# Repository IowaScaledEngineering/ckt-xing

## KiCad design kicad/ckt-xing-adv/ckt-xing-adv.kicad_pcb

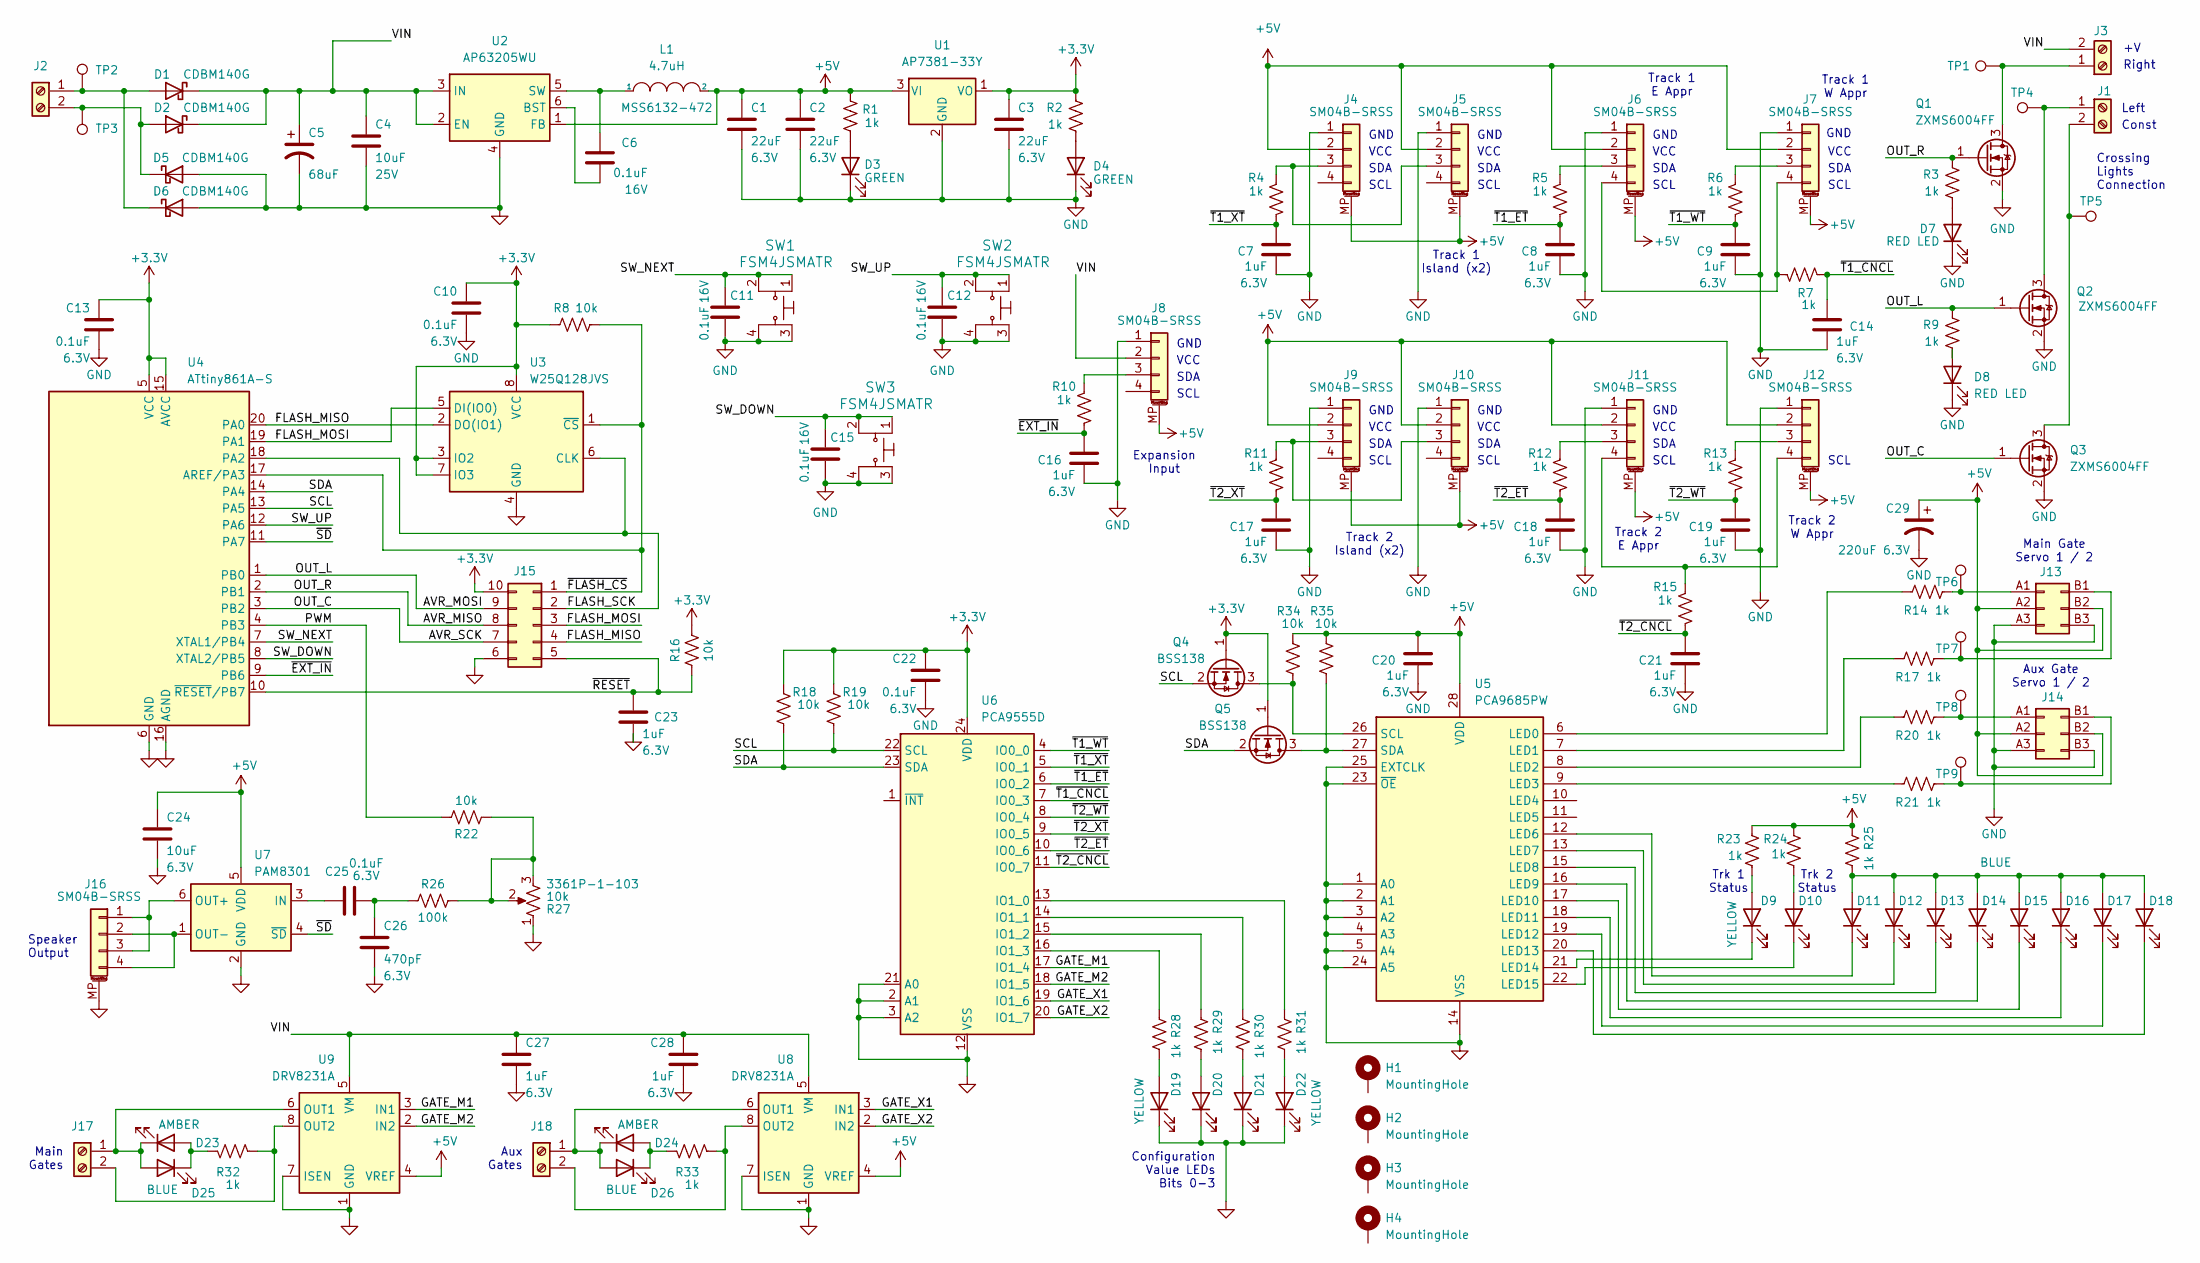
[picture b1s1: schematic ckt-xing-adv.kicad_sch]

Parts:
C1, C2, C3: 22uF; C_0805_2012Metric; Voltage 6.3V
C4: 10uF; C_0805_2012Metric; Voltage 25V
C5: 68uF; CP_Elec_6.3x5.8
C6, C11, C12, C15: 0.1uF; C_0805_2012Metric; Voltage 16V
C7, C8, C9, C14, C16, C17, C18, C19, C20, C21, C23, C27, C28: 1uF; C_0805_2012Metric; Voltage 6.3V
C10, C13, C22, C25: 0.1uF; C_0805_2012Metric; Voltage 6.3V
C24: 10uF; C_0805_2012Metric; Voltage 6.3V
C26: 470pF; C_0805_2012Metric; Voltage 6.3V
C29: 220uF 6.3V; CP_Elec_6.3x5.8
D1, D2, D5, D6: CDBM140G; SOD-123T
D3, D4: GREEN; LED_0805_2012Metric
D7, D8: RED LED; LED_0805_2012Metric
D9, D10, D11, D12, D13, D14, D16, D17, D18, D19, D20, D21, D22: YELLOW; LED_0805_2012Metric
D15, D25, D26: BLUE; LED_0805_2012Metric
D23, D24: AMBER; LED_0805_2012Metric
H1, H2, H3, H4: MountingHole; MountingHole_3.2mm_M3_Pad
J1, J2, J3, J17, J18: Screw_Terminal_01x02; TerminalBlock_RND_205-00012_1x02_P5.00mm_Horizontal
J4, J5, J6, J7, J8, J9, J10, J11, J12, J16: SM04B-SRSS; JST_SH_SM04B-SRSS-TB_1x04-1MP_P1.00mm_Horizontal
J13, J14: Conn_02x03_Row_Letter_First; MOLEX_15910060
J15: Conn_02x05_Counter_Clockwise; Tag-Connect_TC2050-IDC-FP_2x05_P1.27mm_Vertical
L1: 4.7uH; MSS6132-xxxMLC
Q1, Q2, Q3: ZXMS6004FF; SOT-23
Q4, Q5: BSS138; SOT-23
R1, R2, R3, R4, R5, R6, R7, R9, R10, R11, R12, R13, R14, R15, R17, R20, R21, R23, R24, R25, R28, R29, R30, R31, R32, R33: 1k; R_0805_2012Metric
R8, R16, R18, R19, R22, R34, R35: 10k; R_0805_2012Metric
R26: 100k; R_0805_2012Metric
R27: 10k; POT_3361P_BRN
SW1, SW2, SW3: FSM4JSMATR; TE_FSM4JSMA; MPN FSM4JSMATR; Digi-Key_PN 450-1759-1-ND
TP1, TP2, TP3, TP4, TP5, TP6, TP7, TP8, TP9: TestPoint; TestPoint_Pad_D2.0mm
U1: AP7381-33Y; SOT-89-3
U2: AP63205WU; TSOT-23-6
U3: W25Q128JVS; SOIC-8_5.3x6.2mm_P1.27mm
U4: ATtiny861A-S; SOIC-20W_7.5x12.8mm_P1.27mm
U5: PCA9685PW; TSSOP-28_4.4x9.7mm_P0.65mm
U6: PCA9555D; TSSOP-24_4.4x7.8mm_P0.65mm
U7: PAM8301; SOT-23-6
U8, U9: DRV8231A; Texas_HTSOP-8-1EP_3.9x4.9mm_P1.27mm_EP2.95x4.9mm_Mask2.4x3.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

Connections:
+3.3V: C3.1, C10.1, C13.1, C22.1, J15.10, Q4.1 (G), Q5.1 (G), R2.2, R8.1, R16.2, R18.2, R19.2, U1.1 (VO), U3.3 (IO2), U3.7 (IO3), U3.8 (VCC), U4.5 (VCC), U4.15 (AVCC), U6.24 (VDD)
+5V: C1.1, C2.1, C20.1, C24.1, C29.1, J4.2, J4.MP (MountPin), J5.2, J5.MP (MountPin), J6.2, J6.MP (MountPin), J7.2, J7.MP (MountPin), J8.MP (MountPin), J9.2, J9.MP (MountPin), J10.2, J10.MP (MountPin), J11.2, J11.MP (MountPin), J12.2, J12.MP (MountPin), J13.A2 (Pin_a2), J13.B2 (Pin_b2), J14.A2 (Pin_a2), J14.B2 (Pin_b2), L1.2, R1.2, R23.1, R24.1, R25.1, R34.2, R35.2, U1.3 (VI), U2.1 (FB), U5.28 (VDD), U7.5 (VDD), U8.4 (VREF), U9.4 (VREF)
/AVR_MISO: J15.8, Q1.1 (G), R3.2, U4.2 (PB1)
/AVR_MOSI: J15.9, Q2.1 (G), R9.2, U4.1 (PB0)
/AVR_SCK: J15.7, Q3.1 (G), U4.3 (PB2)
/FLASH_MISO: J15.4, U3.2 (DO(IO1)), U4.20 (PA0)
/FLASH_MOSI: J15.3, U3.5 (DI(IO0)), U4.19 (PA1)
/FLASH_SCK: J15.2, U3.6 (CLK), U4.18 (PA2)
/GATE_M1: U6.17 (IO1_4), U9.3 (IN1)
/GATE_M2: U6.18 (IO1_5), U9.2 (IN2)
/GATE_X1: U6.19 (IO1_6), U8.3 (IN1)
/GATE_X2: U6.20 (IO1_7), U8.2 (IN2)
/PWM: R22.2, U4.4 (PB3)
/SCL: Q4.2 (S), R19.1, U4.13 (PA5), U6.22 (SCL)
/SDA: Q5.2 (S), R18.1, U4.14 (PA4), U6.23 (SDA)
/SW_DOWN: C15.1, SW3.1, SW3.2, U4.8 (XTAL2/PB5)
/SW_NEXT: C11.1, SW1.1, SW1.2, U4.7 (XTAL1/PB4)
/SW_UP: C12.1, SW2.1, SW2.2, U4.12 (PA6)
/VIN: C4.1, C5.1, C27.1, C28.1, D1.1 (K), D2.1 (K), J3.2, J8.2, U2.2 (EN), U2.3 (IN), U8.5 (VM), U9.5 (VM)
/~EXT_IN: C16.1, R10.2, U4.9 (PB6)
/~FLASH_CS: J15.1, R8.2, U3.1 (~CS), U4.17 (AREF/PA3)
/~RESET: C23.1, J15.5, R16.1, U4.10 (~RESET/PB7)
/~SD: U4.11 (PA7), U7.4 (~SD)
/~T1_CNCL: C14.1, R7.2, U6.7 (IO0_3)
/~T1_ET: C8.1, R5.2, U6.6 (IO0_2)
/~T1_WT: C9.1, R6.2, U6.4 (IO0_0)
/~T1_XT: C7.1, R4.2, U6.5 (IO0_1)
/~T2_CNCL: C21.1, R15.2, U6.11 (IO0_7)
/~T2_ET: C18.1, R12.2, U6.10 (IO0_6)
/~T2_WT: C19.1, R13.2, U6.8 (IO0_4)
/~T2_XT: C17.1, R11.2, U6.9 (IO0_5)
GND: C1.2, C2.2, C3.2, C4.2, C5.2, C7.2, C8.2, C9.2, C10.2, C11.2, C12.2, C13.2, C14.2, C15.2, C16.2, C17.2, C18.2, C19.2, C20.2, C21.2, C22.2, C23.2, C24.2, C26.2, C27.2, C28.2, C29.2, D3.1 (K), D4.1 (K), D5.2 (A), D6.2 (A), D7.1 (K), D8.1 (K), D19.1 (K), D20.1 (K), D21.1 (K), D22.1 (K), J4.1, J5.1, J6.1, J7.1, J8.1, J9.1, J10.1, J11.1, J12.1, J13.A3 (Pin_a3), J13.B3 (Pin_b3), J14.A3 (Pin_a3), J14.B3 (Pin_b3), J15.6, J16.MP (MountPin), Q1.2 (S), Q2.2 (S), Q3.2 (S), R27.1, SW1.3, SW1.4, SW2.3, SW2.4, SW3.3, SW3.4, U1.2 (GND), U2.4 (GND), U3.4 (GND), U4.6 (GND), U4.16 (AGND), U5.1 (A0), U5.2 (A1), U5.3 (A2), U5.4 (A3), U5.5 (A4), U5.14 (VSS), U5.23 (~OE), U5.24 (A5), U5.25 (EXTCLK), U6.2 (A1), U6.3 (A2), U6.12 (VSS), U6.21 (A0), U7.2 (GND), U8.1 (GND), U8.7 (ISEN), U8.9 (GND), U9.1 (GND), U9.7 (ISEN), U9.9 (GND)
unnamed: C25.2, C26.1, R26.1
unnamed: D1.2 (A), D6.1 (K), J2.1, TP2.1
unnamed: D2.2 (A), D5.1 (K), J2.2, TP3.1
unnamed: D3.2 (A), R1.1
unnamed: D4.2 (A), R2.1
unnamed: D7.2 (A), R3.1
unnamed: D8.2 (A), R9.1
unnamed: D9.2 (A), R23.2
unnamed: D9.1 (K), U5.21 (LED14)
unnamed: D10.2 (A), R24.2
unnamed: D10.1 (K), U5.22 (LED15)
unnamed: D11.2 (A), D12.2 (A), D13.2 (A), D14.2 (A), D15.2 (A), D16.2 (A), D17.2 (A), D18.2 (A), R25.2
unnamed: D11.1 (K), U5.12 (LED6)
unnamed: D12.1 (K), U5.13 (LED7)
unnamed: D13.1 (K), U5.15 (LED8)
unnamed: D14.1 (K), U5.16 (LED9)
unnamed: D15.1 (K), U5.17 (LED10)
unnamed: D16.1 (K), U5.18 (LED11)
unnamed: D17.1 (K), U5.19 (LED12)
unnamed: D18.1 (K), U5.20 (LED13)
unnamed: D19.2 (A), R28.2
unnamed: D20.2 (A), R29.2
unnamed: D21.2 (A), R30.2
unnamed: D22.2 (A), R31.2
unnamed: D23.2 (A), D25.1 (K), R32.1
unnamed: D23.1 (K), D25.2 (A), J17.1, U9.6 (OUT1)
unnamed: D24.2 (A), D26.1 (K), R33.1
unnamed: D24.1 (K), D26.2 (A), J18.1, U8.6 (OUT1)
unnamed: J1.1, Q2.3 (D), TP4.1
unnamed: J1.2, Q3.3 (D), TP5.1
unnamed: J3.1, Q1.3 (D), TP1.1
unnamed: J4.3, J5.3, R4.1
unnamed: J6.3, R5.1
unnamed: J6.4, J7.4, R7.1
unnamed: J7.3, R6.1
unnamed: J8.3, R10.1
unnamed: J9.3, J10.3, R11.1
unnamed: J11.3, R12.1
unnamed: J11.4, J12.4, R15.1
unnamed: J12.3, R13.1
unnamed: J13.A1 (Pin_a1), R14.2, TP6.1
unnamed: J13.B1 (Pin_b1), R17.2, TP7.1
unnamed: J14.A1 (Pin_a1), R20.2, TP8.1
unnamed: J14.B1 (Pin_b1), R21.2, TP9.1
unnamed: J16.1, J16.3, U7.6 (OUT+)
unnamed: J16.2, J16.4, U7.1 (OUT-)
unnamed: J17.2, R32.2, U9.8 (OUT2)
unnamed: J18.2, R33.2, U8.8 (OUT2)
unnamed: Q4.3 (D), R34.1, U5.26 (SCL)
unnamed: Q5.3 (D), R35.1, U5.27 (SDA)
unnamed: R22.1, R26.2, R27.2, R27.3
unnamed: C6.2, U2.6 (BST)
unnamed: C6.1, L1.1, U2.5 (SW)
unnamed: R14.1, U5.6 (LED0)
unnamed: R17.1, U5.7 (LED1)
unnamed: R20.1, U5.8 (LED2)
unnamed: R21.1, U5.9 (LED3)
unnamed: R31.1, U6.13 (IO1_0)
unnamed: R30.1, U6.14 (IO1_1)
unnamed: R29.1, U6.15 (IO1_2)
unnamed: R28.1, U6.16 (IO1_3)
unnamed: C25.1, U7.3 (IN)

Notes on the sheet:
SDA
Track 1 E Appr
Const
SCL
Trk 2 Status
GND
Speaker Output
Track 1 W Appr
Aux Gates
VCC
Track 1 Island (x2)
Left
Crossing Lights Connection
Trk 1 Status
Configuration Value LEDs Bits 0-3
Track 2 E Appr
Aux Gate Servo 1 / 2
Expansion Input
Main Gates
Track 2 W Appr
Right
Track 2 Island (x2)
Main Gate Servo 1 / 2

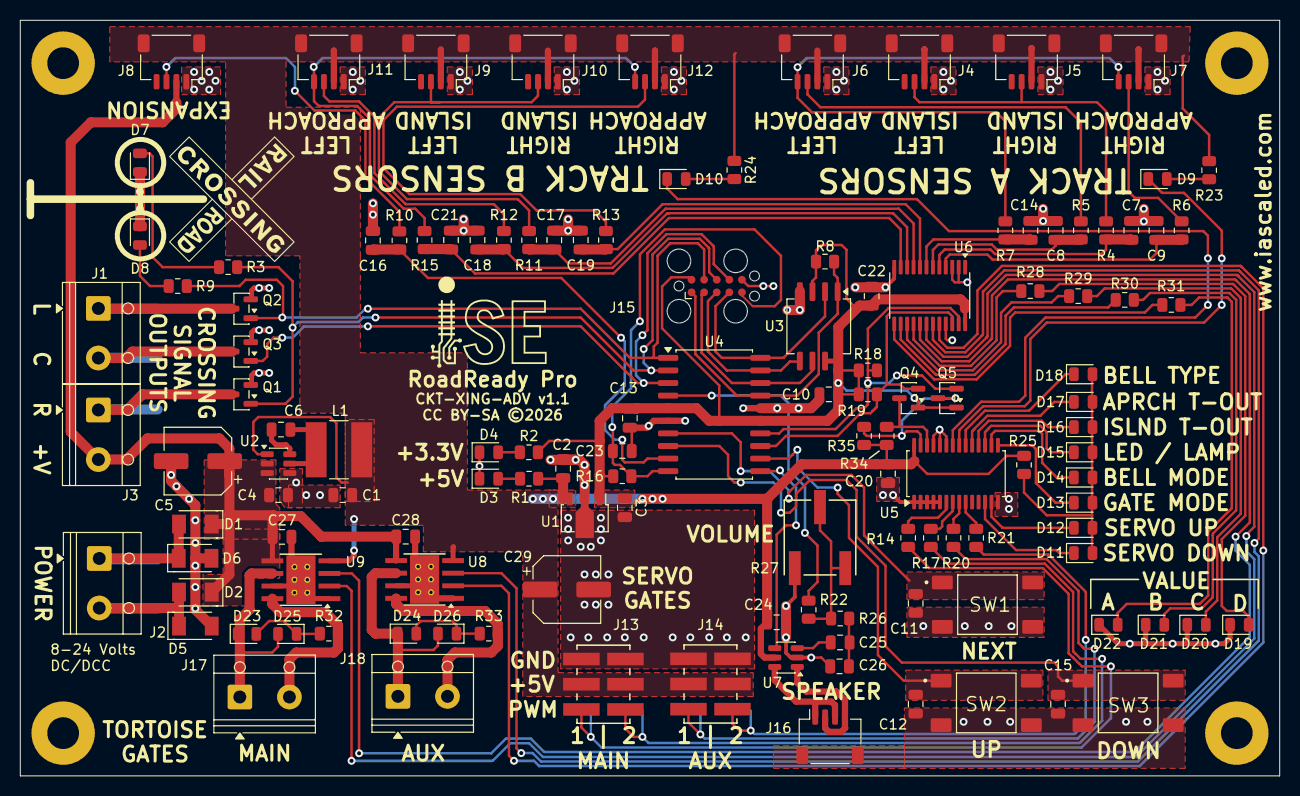
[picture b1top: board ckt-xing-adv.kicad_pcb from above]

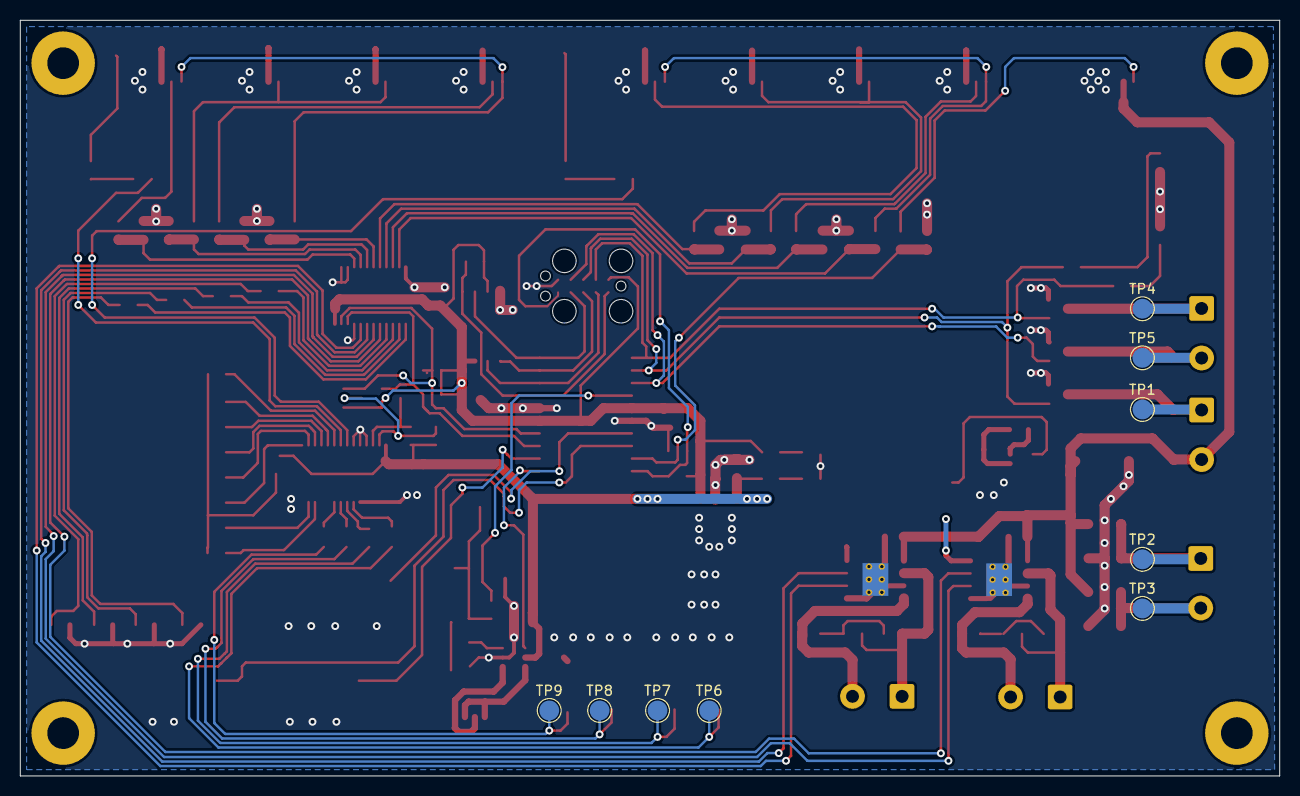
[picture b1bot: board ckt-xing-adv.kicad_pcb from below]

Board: 2 copper layers, 127.0 x 76.2 mm, 139 parts (9 on the bottom side), 94 nets.

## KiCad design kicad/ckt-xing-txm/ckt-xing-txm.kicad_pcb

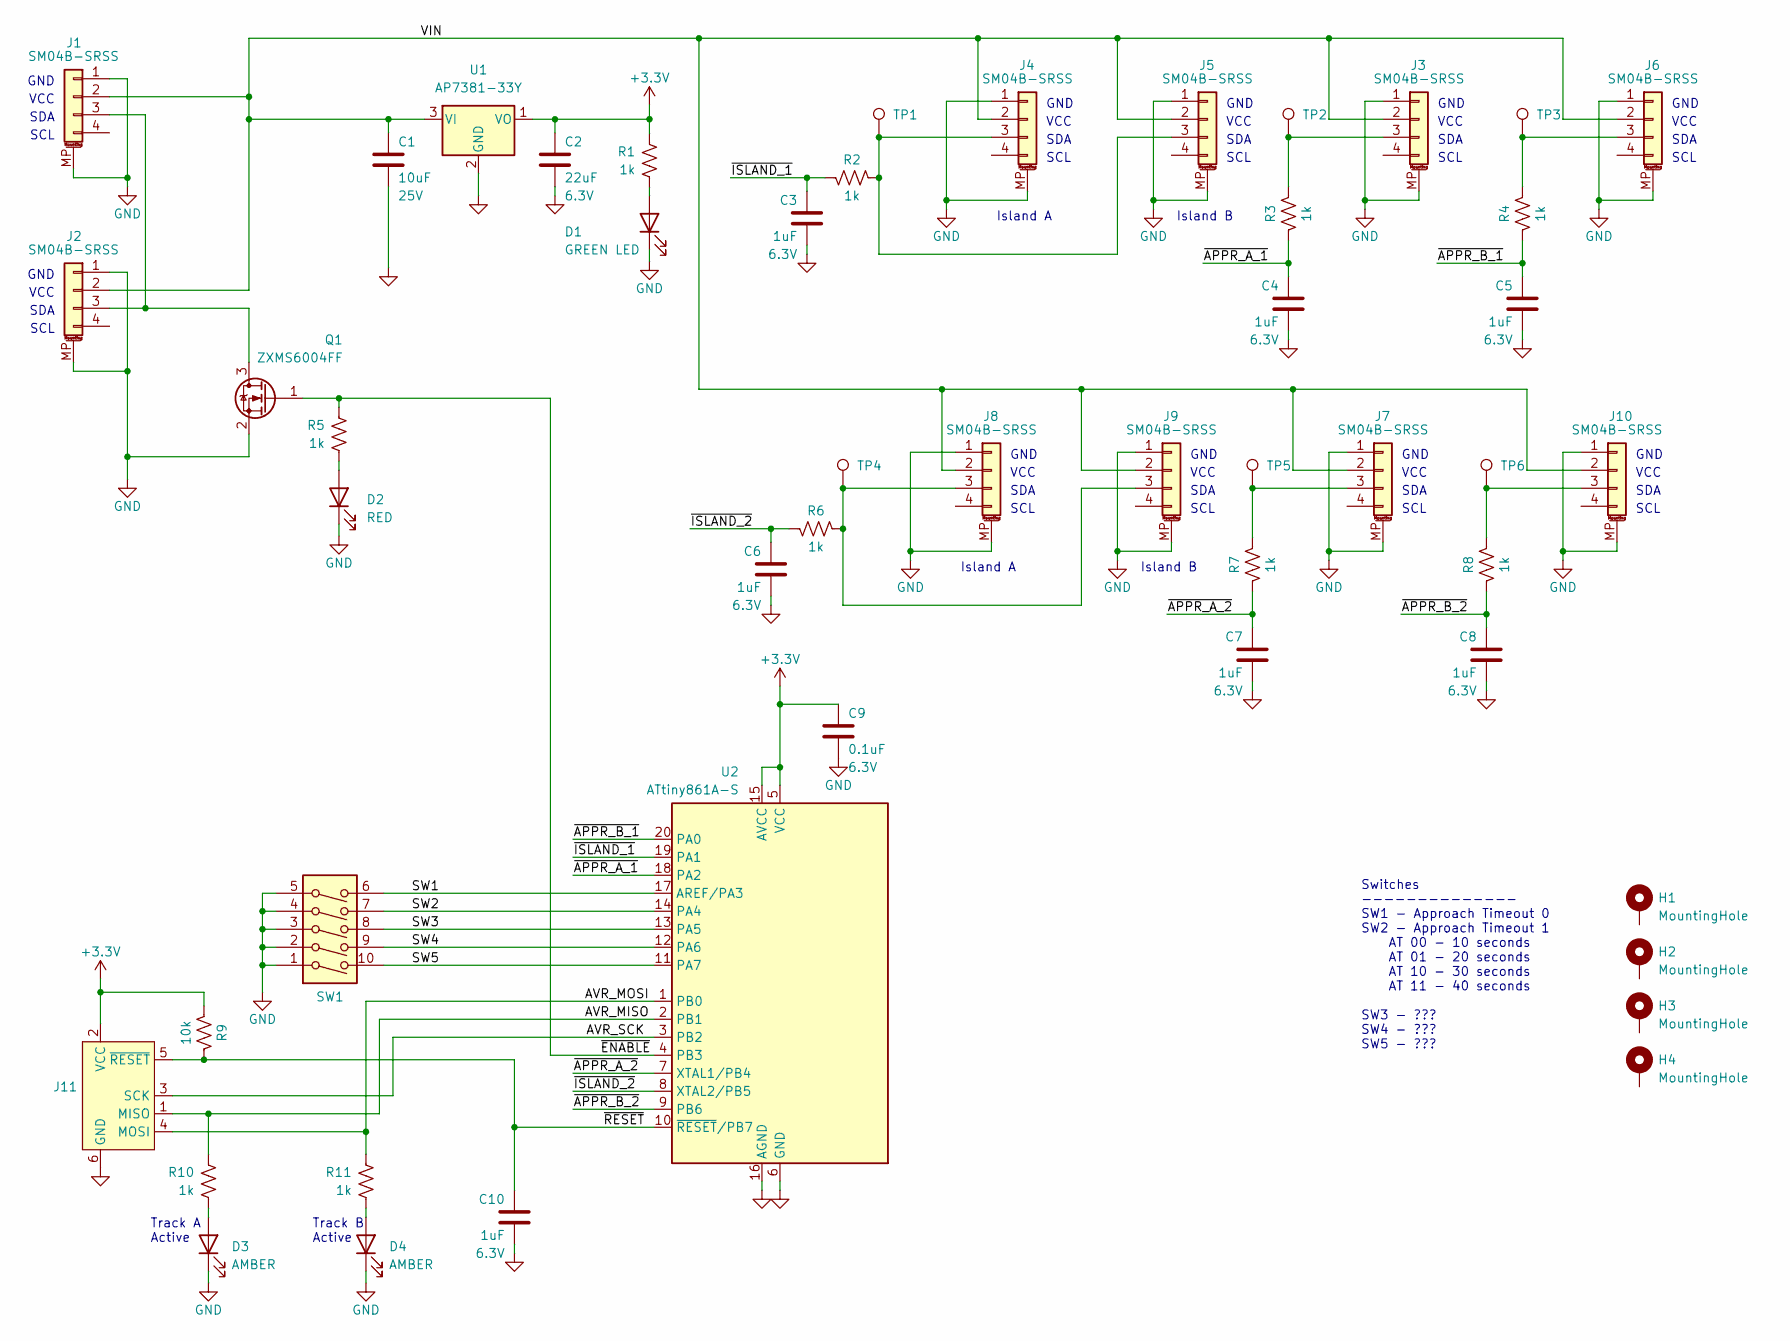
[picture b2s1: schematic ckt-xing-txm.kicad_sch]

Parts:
C1: 10uF; C_0805_2012Metric; Voltage 25V
C2: 22uF; C_0805_2012Metric; Voltage 6.3V
C3, C4, C5, C6, C7, C8, C10: 1uF; C_0805_2012Metric; Voltage 6.3V
C9: 0.1uF; C_0805_2012Metric; Voltage 6.3V
D1: GREEN LED; LED_0805_2012Metric
D2: RED; LED_0805_2012Metric
D3, D4: AMBER; LED_0805_2012Metric
H1, H2, H3, H4: MountingHole; MountingHole_3.2mm_M3_Pad
J1, J2, J3, J4, J5, J6, J7, J8, J9, J10: SM04B-SRSS; JST_SH_SM04B-SRSS-TB_1x04-1MP_P1.00mm_Horizontal
J11: Conn_AVR_TagConnect_TC2030; Tag-Connect_TC2030-IDC-NL_2x03_P1.27mm_Vertical
Q1: ZXMS6004FF; SOT-23
R1, R2, R3, R4, R5, R6, R7, R8, R10, R11: 1k; R_0805_2012Metric
R9: 10k; R_0805_2012Metric
SW1: SW_DIP_x05; CST_219SMT
TP1, TP2, TP3, TP4, TP5, TP6: TestPoint; TestPoint_Pad_D2.0mm
U1: AP7381-33Y; SOT-89-3
U2: ATtiny861A-S; SOIC-20W_7.5x12.8mm_P1.27mm

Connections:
+3.3V: C2.1, C9.1, J11.2 (VCC), R1.2, R9.2, U1.1 (VO), U2.5 (VCC), U2.15 (AVCC)
/AVR_MISO: J11.1 (MISO), R10.2, U2.2 (PB1)
/AVR_MOSI: J11.4 (MOSI), R11.2, U2.1 (PB0)
/AVR_SCK: J11.3 (SCK), U2.3 (PB2)
/SW1: SW1.6, U2.17 (AREF/PA3)
/SW2: SW1.7, U2.14 (PA4)
/SW3: SW1.8, U2.13 (PA5)
/SW4: SW1.9, U2.12 (PA6)
/SW5: SW1.10, U2.11 (PA7)
/VIN: C1.1, J1.2, J2.2, J3.2, J4.2, J5.2, J6.2, J7.2, J8.2, J9.2, J10.2, U1.3 (VI)
/~APPR_A_1: C4.1, R3.2, U2.18 (PA2)
/~APPR_A_2: C7.1, R7.2, U2.7 (XTAL1/PB4)
/~APPR_B_1: C5.1, R4.2, U2.20 (PA0)
/~APPR_B_2: C8.1, R8.2, U2.9 (PB6)
/~ENABLE: Q1.1 (G), R5.2, U2.4 (PB3)
/~ISLAND_1: C3.1, R2.2, U2.19 (PA1)
/~ISLAND_2: C6.1, R6.2, U2.8 (XTAL2/PB5)
/~RESET: C10.1, J11.5 (~RESET), R9.1, U2.10 (~RESET/PB7)
GND: C1.2, C2.2, C3.2, C4.2, C5.2, C6.2, C7.2, C8.2, C9.2, C10.2, D1.1 (K), D2.1 (K), D3.1 (K), D4.1 (K), J1.1, J1.MP (MountPin), J2.1, J2.MP (MountPin), J3.1, J3.MP (MountPin), J4.1, J4.MP (MountPin), J5.1, J5.MP (MountPin), J6.1, J6.MP (MountPin), J7.1, J7.MP (MountPin), J8.1, J8.MP (MountPin), J9.1, J9.MP (MountPin), J10.1, J10.MP (MountPin), J11.6 (GND), Q1.2 (S), SW1.1, SW1.2, SW1.3, SW1.4, SW1.5, U1.2 (GND), U2.6 (GND), U2.16 (AGND)
unnamed: D1.2 (A), R1.1
unnamed: D2.2 (A), R5.1
unnamed: D3.2 (A), R10.1
unnamed: D4.2 (A), R11.1
unnamed: J1.3, J2.3, Q1.3 (D)
unnamed: J3.3, R3.1, TP2.1
unnamed: J6.3, R4.1, TP3.1
unnamed: J7.3, R7.1, TP5.1
unnamed: J8.3, J9.3, R6.1, TP4.1
unnamed: J10.3, R8.1, TP6.1
unnamed: J4.3, J5.3, R2.1, TP1.1

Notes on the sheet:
SCL
Track A Active
GND
VCC
SDA
Island B
Island A
Switches -------------- SW1 - Approach Timeout 0 SW2 - Approach Timeout 1 AT 00 - 10 seconds AT 01 - 20 seconds AT 10 - 30 seconds AT 11 - 40 seconds SW3 - ??? SW4 - ??? SW5 - ???
Track B Active

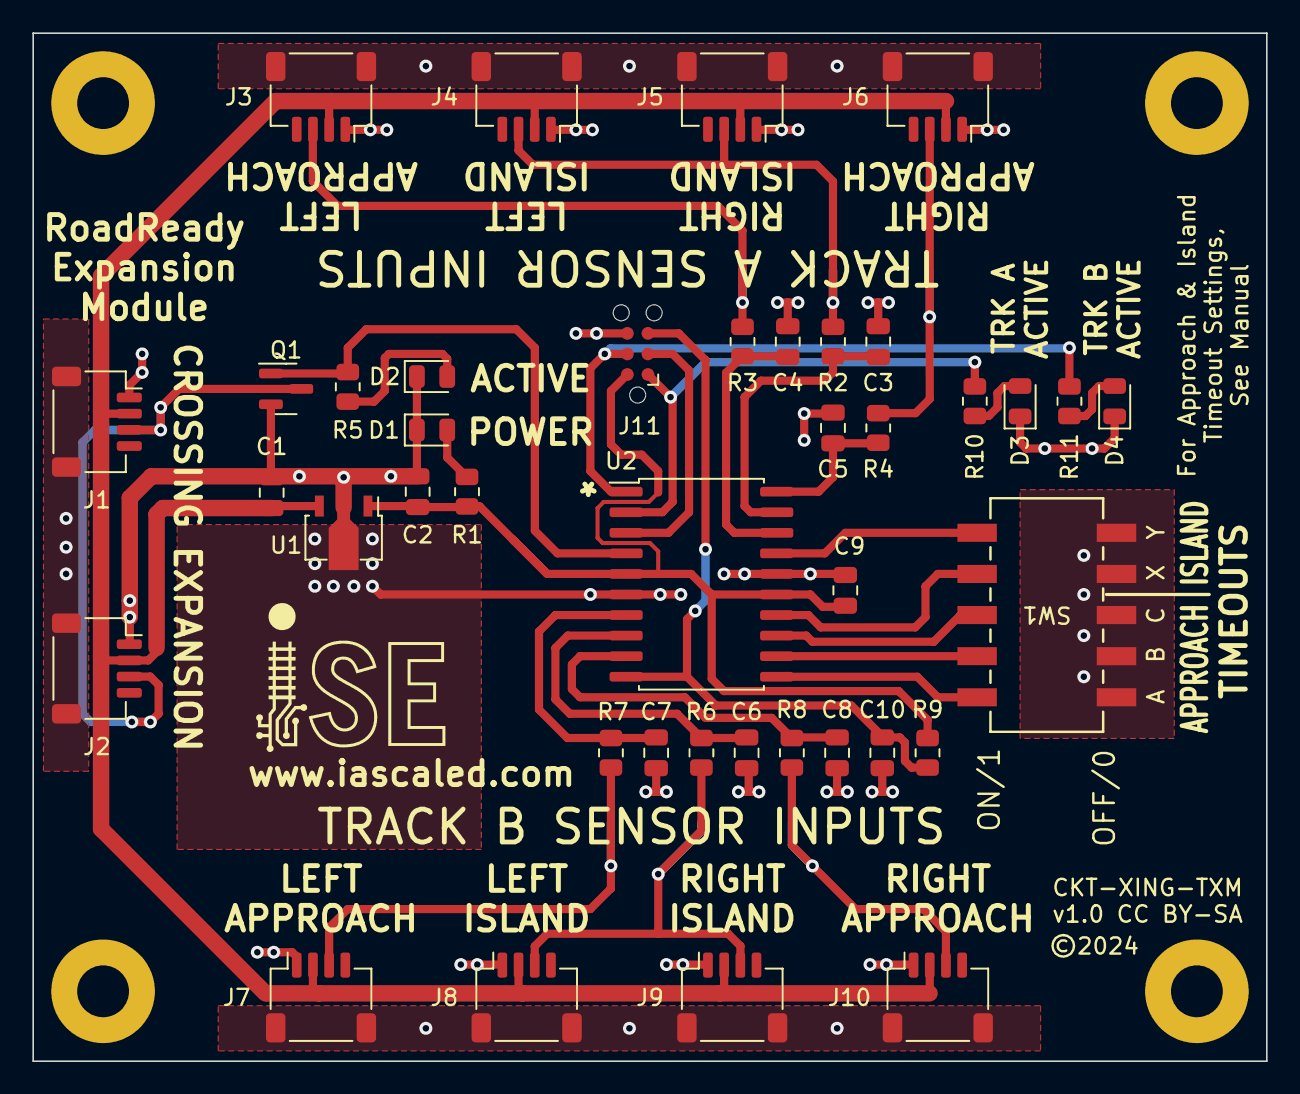
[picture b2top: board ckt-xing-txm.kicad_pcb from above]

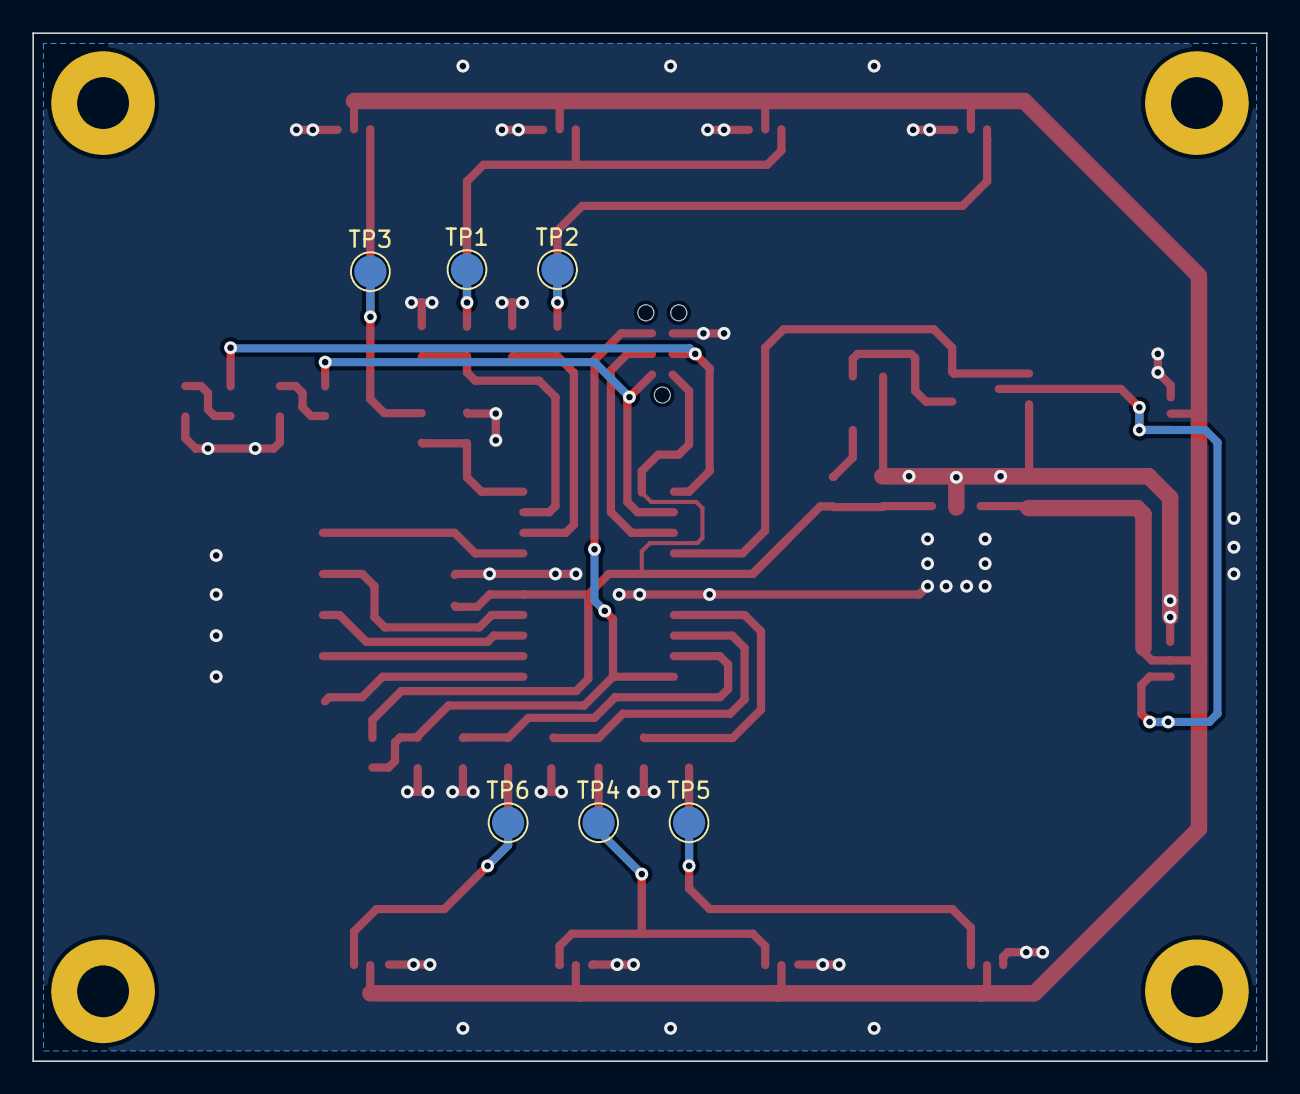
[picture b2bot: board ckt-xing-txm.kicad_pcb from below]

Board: 2 copper layers, 76.2 x 63.5 mm, 50 parts (6 on the bottom side), 30 nets.

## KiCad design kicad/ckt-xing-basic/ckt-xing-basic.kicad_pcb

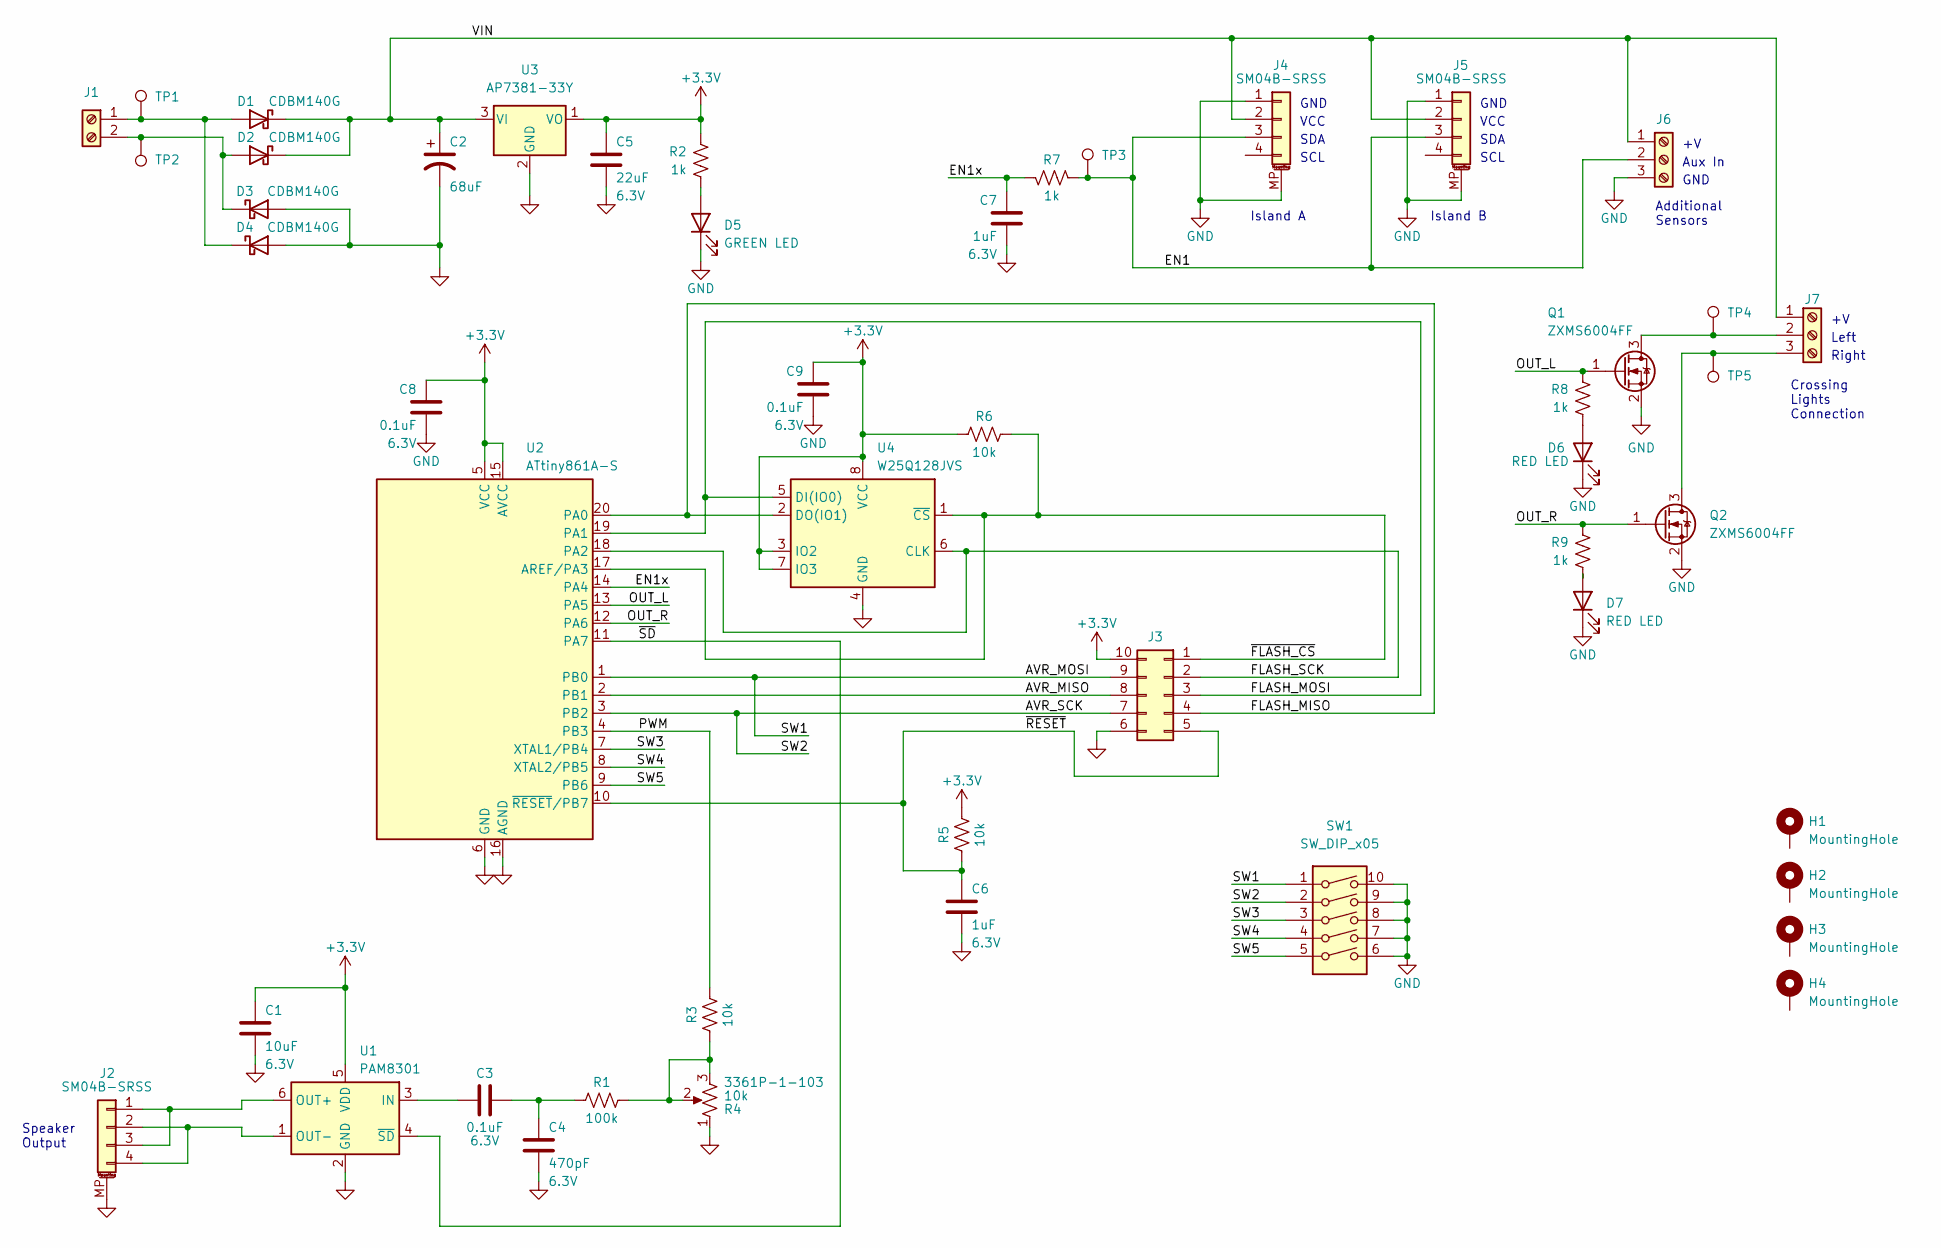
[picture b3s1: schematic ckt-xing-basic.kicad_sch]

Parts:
C1: 10uF; C_0805_2012Metric; Voltage 6.3V
C2: 68uF; CP_Elec_6.3x5.8
C3, C8, C9: 0.1uF; C_0805_2012Metric; Voltage 6.3V
C4: 470pF; C_0805_2012Metric; Voltage 6.3V
C5: 22uF; C_0805_2012Metric; Voltage 6.3V
C6, C7: 1uF; C_0805_2012Metric; Voltage 6.3V
D1, D2, D3, D4: CDBM140G; D_SOD-123
D5: GREEN LED; LED_0805_2012Metric
D6, D7: RED LED; LED_0805_2012Metric
H1, H2, H3, H4: MountingHole; MountingHole_3.2mm_M3_Pad
J1: Screw_Terminal_01x02; TerminalBlock_RND_205-00012_1x02_P5.00mm_Horizontal
J2, J4, J5: SM04B-SRSS; JST_SH_SM04B-SRSS-TB_1x04-1MP_P1.00mm_Horizontal
J3: Conn_02x05_Counter_Clockwise; Tag-Connect_TC2050-IDC-FP_2x05_P1.27mm_Vertical
J6, J7: Screw_Terminal_01x02; TerminalBlock_MetzConnect_Type059_RT06303HBWC_1x03_P3.50mm_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
Q1, Q2: ZXMS6004FF; SOT-23
R1: 100k; R_0805_2012Metric
R2, R7, R8, R9: 1k; R_0805_2012Metric
R3, R5, R6: 10k; R_0805_2012Metric
R4: 10k; POT_3361P_BRN
SW1: SW_DIP_x05; CST_219SMT
TP1, TP2, TP3, TP4, TP5: TestPoint; TestPoint_Pad_D2.0mm
U1: PAM8301; SOT-23-6
U2: ATtiny861A-S; SOIC-20W_7.5x12.8mm_P1.27mm
U3: AP7381-33Y; SOT-89-3
U4: W25Q128JVS; SOIC-8_5.23x5.23mm_P1.27mm

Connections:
+3.3V: C1.1, C5.1, C8.1, C9.1, J3.10, R2.2, R5.2, R6.1, U1.5 (VDD), U2.5 (VCC), U2.15 (AVCC), U3.1 (VO), U4.3 (IO2), U4.7 (IO3), U4.8 (VCC)
/AVR_MISO: J3.8, U2.2 (PB1)
/AVR_MOSI: J3.9, SW1.1, U2.1 (PB0)
/AVR_SCK: J3.7, SW1.2, U2.3 (PB2)
/EN1: J4.3, J5.3, J6.2, R7.1, TP3.1
/EN1x: C7.1, R7.2, U2.14 (PA4)
/FLASH_MISO: J3.4, U2.20 (PA0), U4.2 (DO(IO1))
/FLASH_MOSI: J3.3, U2.19 (PA1), U4.5 (DI(IO0))
/FLASH_SCK: J3.2, U2.18 (PA2), U4.6 (CLK)
/OUT_L: Q1.1 (G), R8.2, U2.13 (PA5)
/OUT_R: Q2.1 (G), R9.2, U2.12 (PA6)
/PWM: R3.2, U2.4 (PB3)
/SW3: SW1.3, U2.7 (XTAL1/PB4)
/SW4: SW1.4, U2.8 (XTAL2/PB5)
/SW5: SW1.5, U2.9 (PB6)
/VIN: C2.1, D1.1 (K), D2.1 (K), J4.2, J5.2, J6.1, J7.1, U3.3 (VI)
/~FLASH_CS: J3.1, R6.2, U2.17 (AREF/PA3), U4.1 (~CS)
/~RESET: C6.1, J3.5, R5.1, U2.10 (~RESET/PB7)
/~SD: U1.4 (~SD), U2.11 (PA7)
GND: C1.2, C2.2, C4.2, C5.2, C6.2, C7.2, C8.2, C9.2, D3.2 (A), D4.2 (A), D5.1 (K), D6.1 (K), D7.1 (K), J2.MP (MountPin), J3.6, J4.1, J4.MP (MountPin), J5.1, J5.MP (MountPin), J6.3, Q1.2 (S), Q2.2 (S), R4.1, SW1.6, SW1.7, SW1.8, SW1.9, SW1.10, U1.2 (GND), U2.6 (GND), U2.16 (AGND), U3.2 (GND), U4.4 (GND)
unnamed: C3.1, U1.3 (IN)
unnamed: C3.2, C4.1, R1.1
unnamed: D1.2 (A), D4.1 (K), J1.1, TP1.1
unnamed: D2.2 (A), D3.1 (K), J1.2, TP2.1
unnamed: D5.2 (A), R2.1
unnamed: D6.2 (A), R8.1
unnamed: D7.2 (A), R9.1
unnamed: J2.1, J2.3, U1.6 (OUT+)
unnamed: J2.2, J2.4, U1.1 (OUT-)
unnamed: J7.2, Q1.3 (D), TP4.1
unnamed: J7.3, Q2.3 (D), TP5.1
unnamed: R1.2, R3.1, R4.2, R4.3

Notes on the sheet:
Additional Sensors
GND
Island B
SDA
Speaker Output
Island A
VCC
Right
Crossing Lights Connection
SCL
Aux In
Left

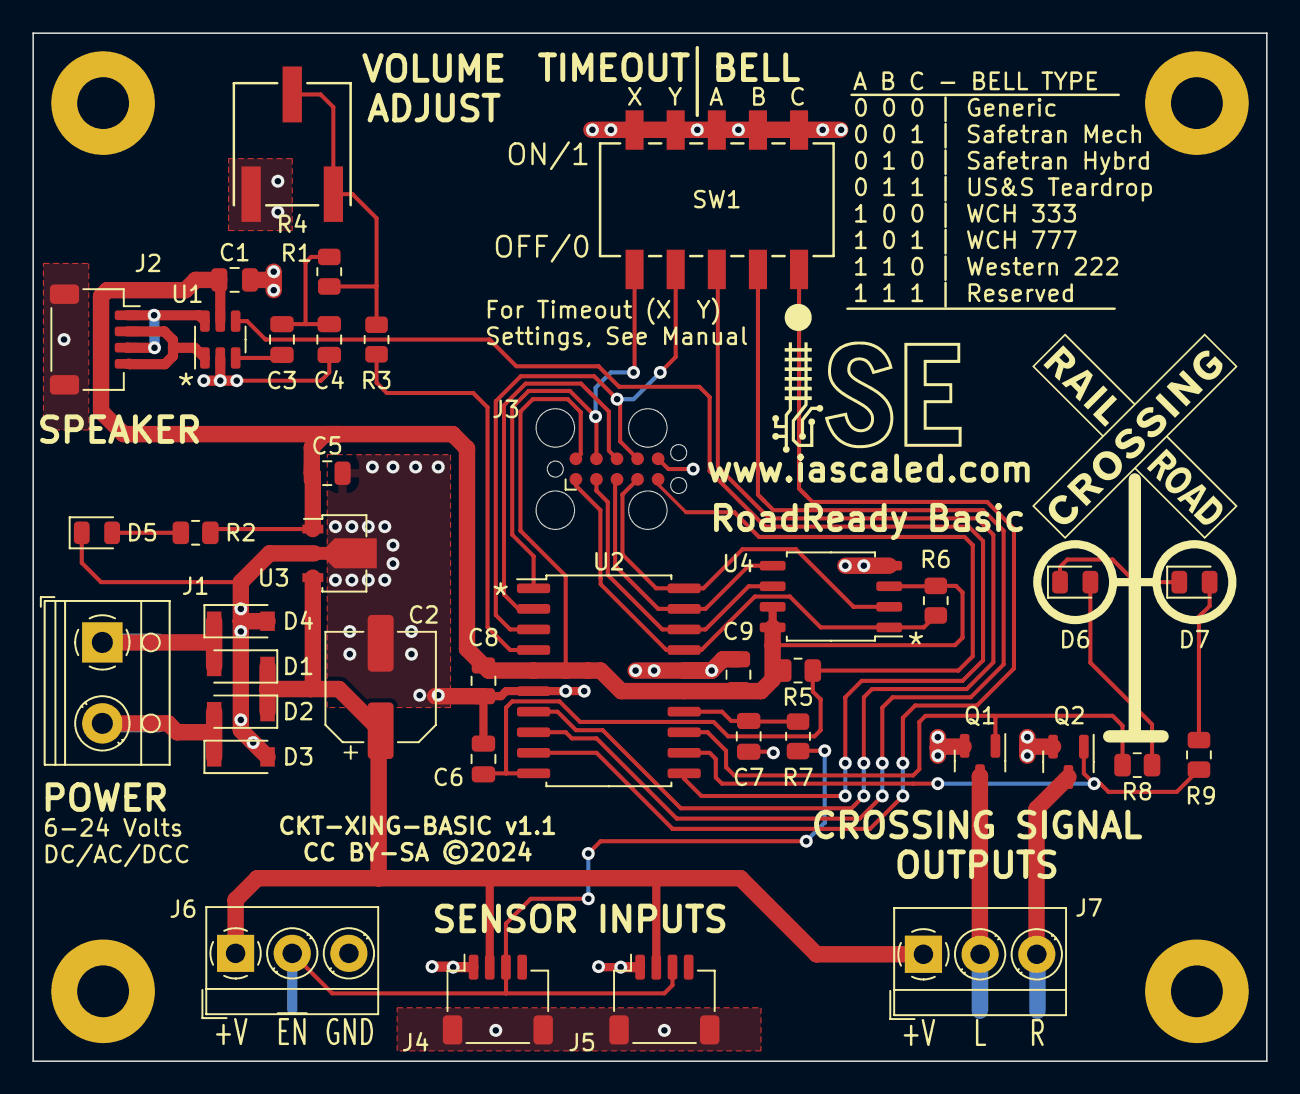
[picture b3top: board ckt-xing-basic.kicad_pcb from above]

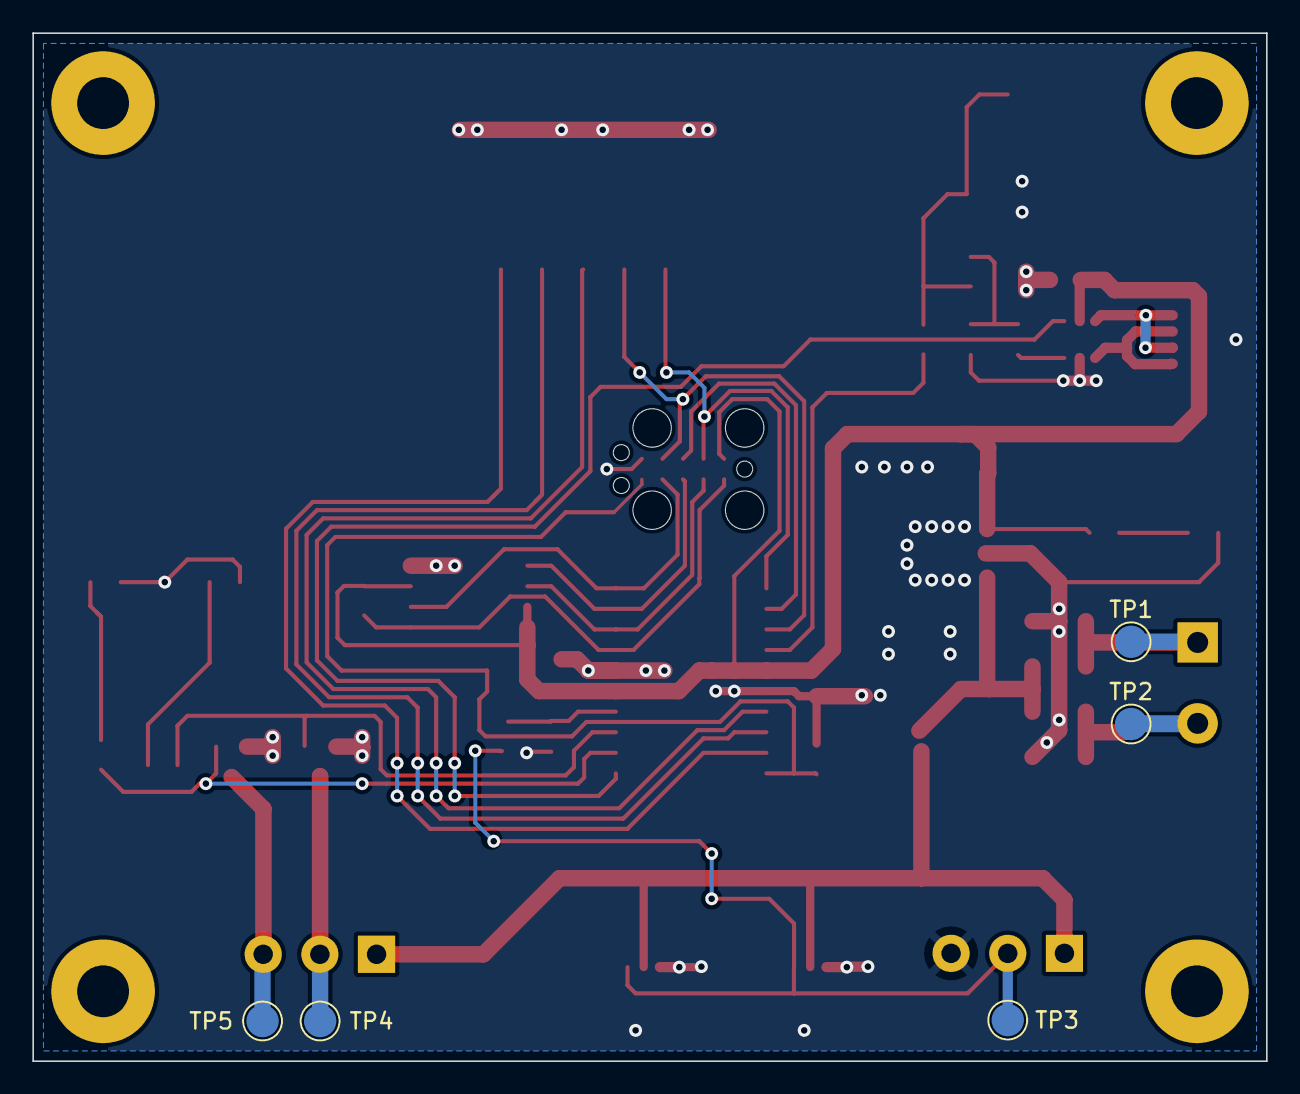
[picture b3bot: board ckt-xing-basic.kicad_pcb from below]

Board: 2 copper layers, 76.2 x 63.5 mm, 48 parts (5 on the bottom side), 32 nets.

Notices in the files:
kicad/ckt-xing-adv/ckt-xing-adv.kicad_pcb:
CC BY-SA ©2026
kicad/ckt-xing-basic/ckt-xing-basic.kicad_pcb:
CC BY-SA ©2024
kicad/ckt-xing-txm/ckt-xing-txm.kicad_pcb:
v1.0 CC BY-SA
©2024
